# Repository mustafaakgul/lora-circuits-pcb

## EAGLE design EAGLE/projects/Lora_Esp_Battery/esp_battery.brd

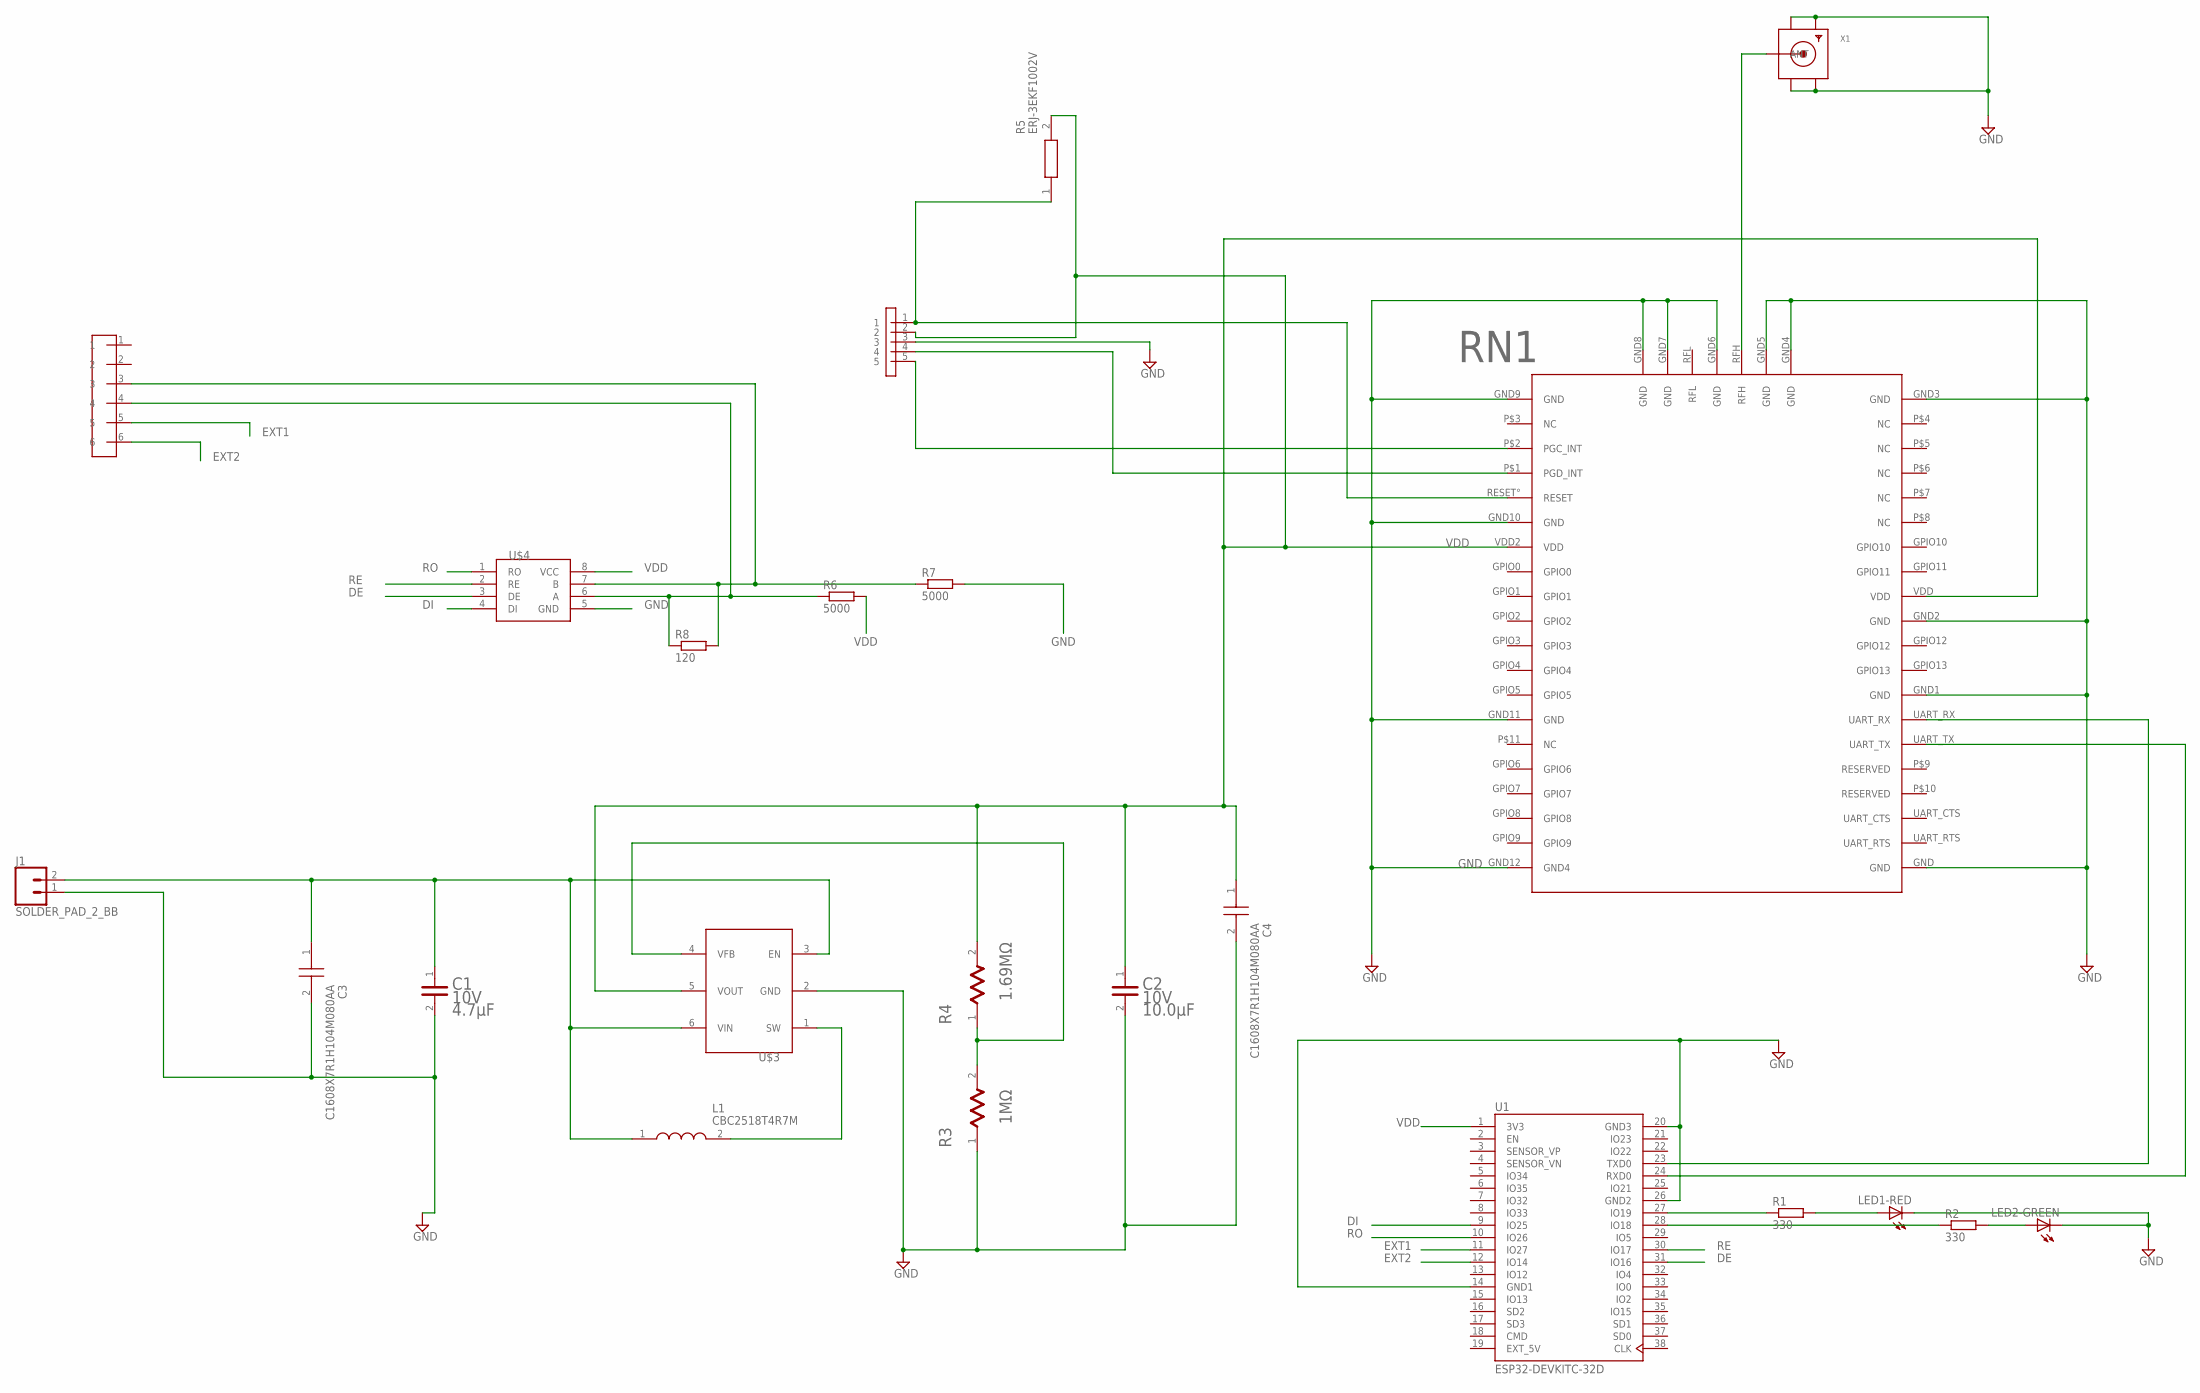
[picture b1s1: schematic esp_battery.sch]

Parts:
C1: KEMET_C0603C475K8PACTUKEMET_C0603C475K8PACTU_0_0; KEMET_C0603C475K8PACTU_0
C2: TDK_C1608X5R1A106M080ACTDK_C1608X5R1A106M080AC_0_0; TDK_C1608X5R1A106M080AC_0
C3, C4: C1608X7R1H104M080AA; CAPC1608X80N
J1: SOLDER_PAD_2_BB; SOLDER_PAD_2
L1: CBC2518T4R7M; INDC2518X200N
LED1-RED, LED2-GREEN: LEDCHIP-LED0603; CHIP-LED0603
R1, R2: 330; R0603
R3: STACKPOLE_RMCF0603FT1M00STACKPOLE_RMCF0603FT1M00_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; STACKPOLE_RMCF0603FT1M00_1
R4: VISHAY_CRCW06031M69FKEAVISHAY_CRCW06031M69FKEA_0_1; VISHAY_CRCW06031M69FKEA_1
R5: ERJ-3EKF1002V; RESC1608X55N
R6, R7: 5000; R0805
R8: 120; R0805
RN1: NEW_RN2483
U1: ESP32-DEVKITC-32D; MODULE_ESP32-DEVKITC-32D
U$1: CONNECTOR62; CONNECTOR6
U$2: ICSP52; ICSP
U$3: MCP16252
U$4: AMD3485E
X1: SMACONNECTOR_EDGE; SMA_EDGELAUNCH

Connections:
DE: U1.31 (IO16), U$4.3 (DE)
DI: U1.9 (IO25), U$4.4 (DI)
EXT1: U1.11 (IO27), U$1.5
EXT2: U1.12 (IO14), U$1.6
EXT_5V: U1.19 (EXT_5V)
GND: C1.2, C2.2, C3.2, C4.2, J1.1, LED1-RED.C, LED2-GREEN.C, R3.1, R7.2, RN1.GND, RN1.GND1 (GND), RN1.GND2 (GND), RN1.GND3 (GND), RN1.GND4 (GND), RN1.GND5 (GND), RN1.GND6 (GND), RN1.GND7 (GND), RN1.GND8 (GND), RN1.GND9 (GND), RN1.GND10 (GND), RN1.GND11 (GND), RN1.GND12 (GND4), U1.14 (GND1), U1.20 (GND3), U1.26 (GND2), U$2.3, U$3.2 (GND), U$4.5 (GND), X1.GND@1 (GND4), X1.GND@2 (GND3), X1.GND@3 (GND2), X1.GND@4 (GND1)
unnamed: R1.1, U1.27 (IO19)
unnamed: LED1-RED.A, R1.2
unnamed: C1.1, C3.1, J1.2, L1.1, U$3.3 (EN), U$3.6 (VIN)
unnamed: LED2-GREEN.A, R2.2
unnamed: R2.1, U1.28 (IO18)
unnamed: R5.1, RN1.RESET° (RESET), U$2.1
unnamed: RN1.RFH, X1.P (ANT)
unnamed: L1.2, U$3.1 (SW)
unnamed: R3.2, R4.1, U$3.4 (VFB)
unnamed: RN1.P$1 (PGD_INT), U$2.4
unnamed: RN1.P$2 (PGC_INT), U$2.5
unnamed: RN1.UART_RX, U1.23 (TXD0)
unnamed: R7.1, R8.2, U$1.3, U$4.7 (B)
unnamed: R6.1, R8.1, U$1.4, U$4.6 (A)
unnamed: RN1.UART_TX, U1.24 (RXD0)
RE: U1.30 (IO17), U$4.2 (RE)
RO: U1.10 (IO26), U$4.1 (RO)
VDD: C2.1, C4.1, R4.2, R5.2, R6.2, RN1.VDD, RN1.VDD2 (VDD), U1.1 (3V3), U$2.2, U$3.5 (VOUT), U$4.8 (VCC)

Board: 2 copper layers, 23 parts (1 on the bottom side), 23 nets, no tracks yet.

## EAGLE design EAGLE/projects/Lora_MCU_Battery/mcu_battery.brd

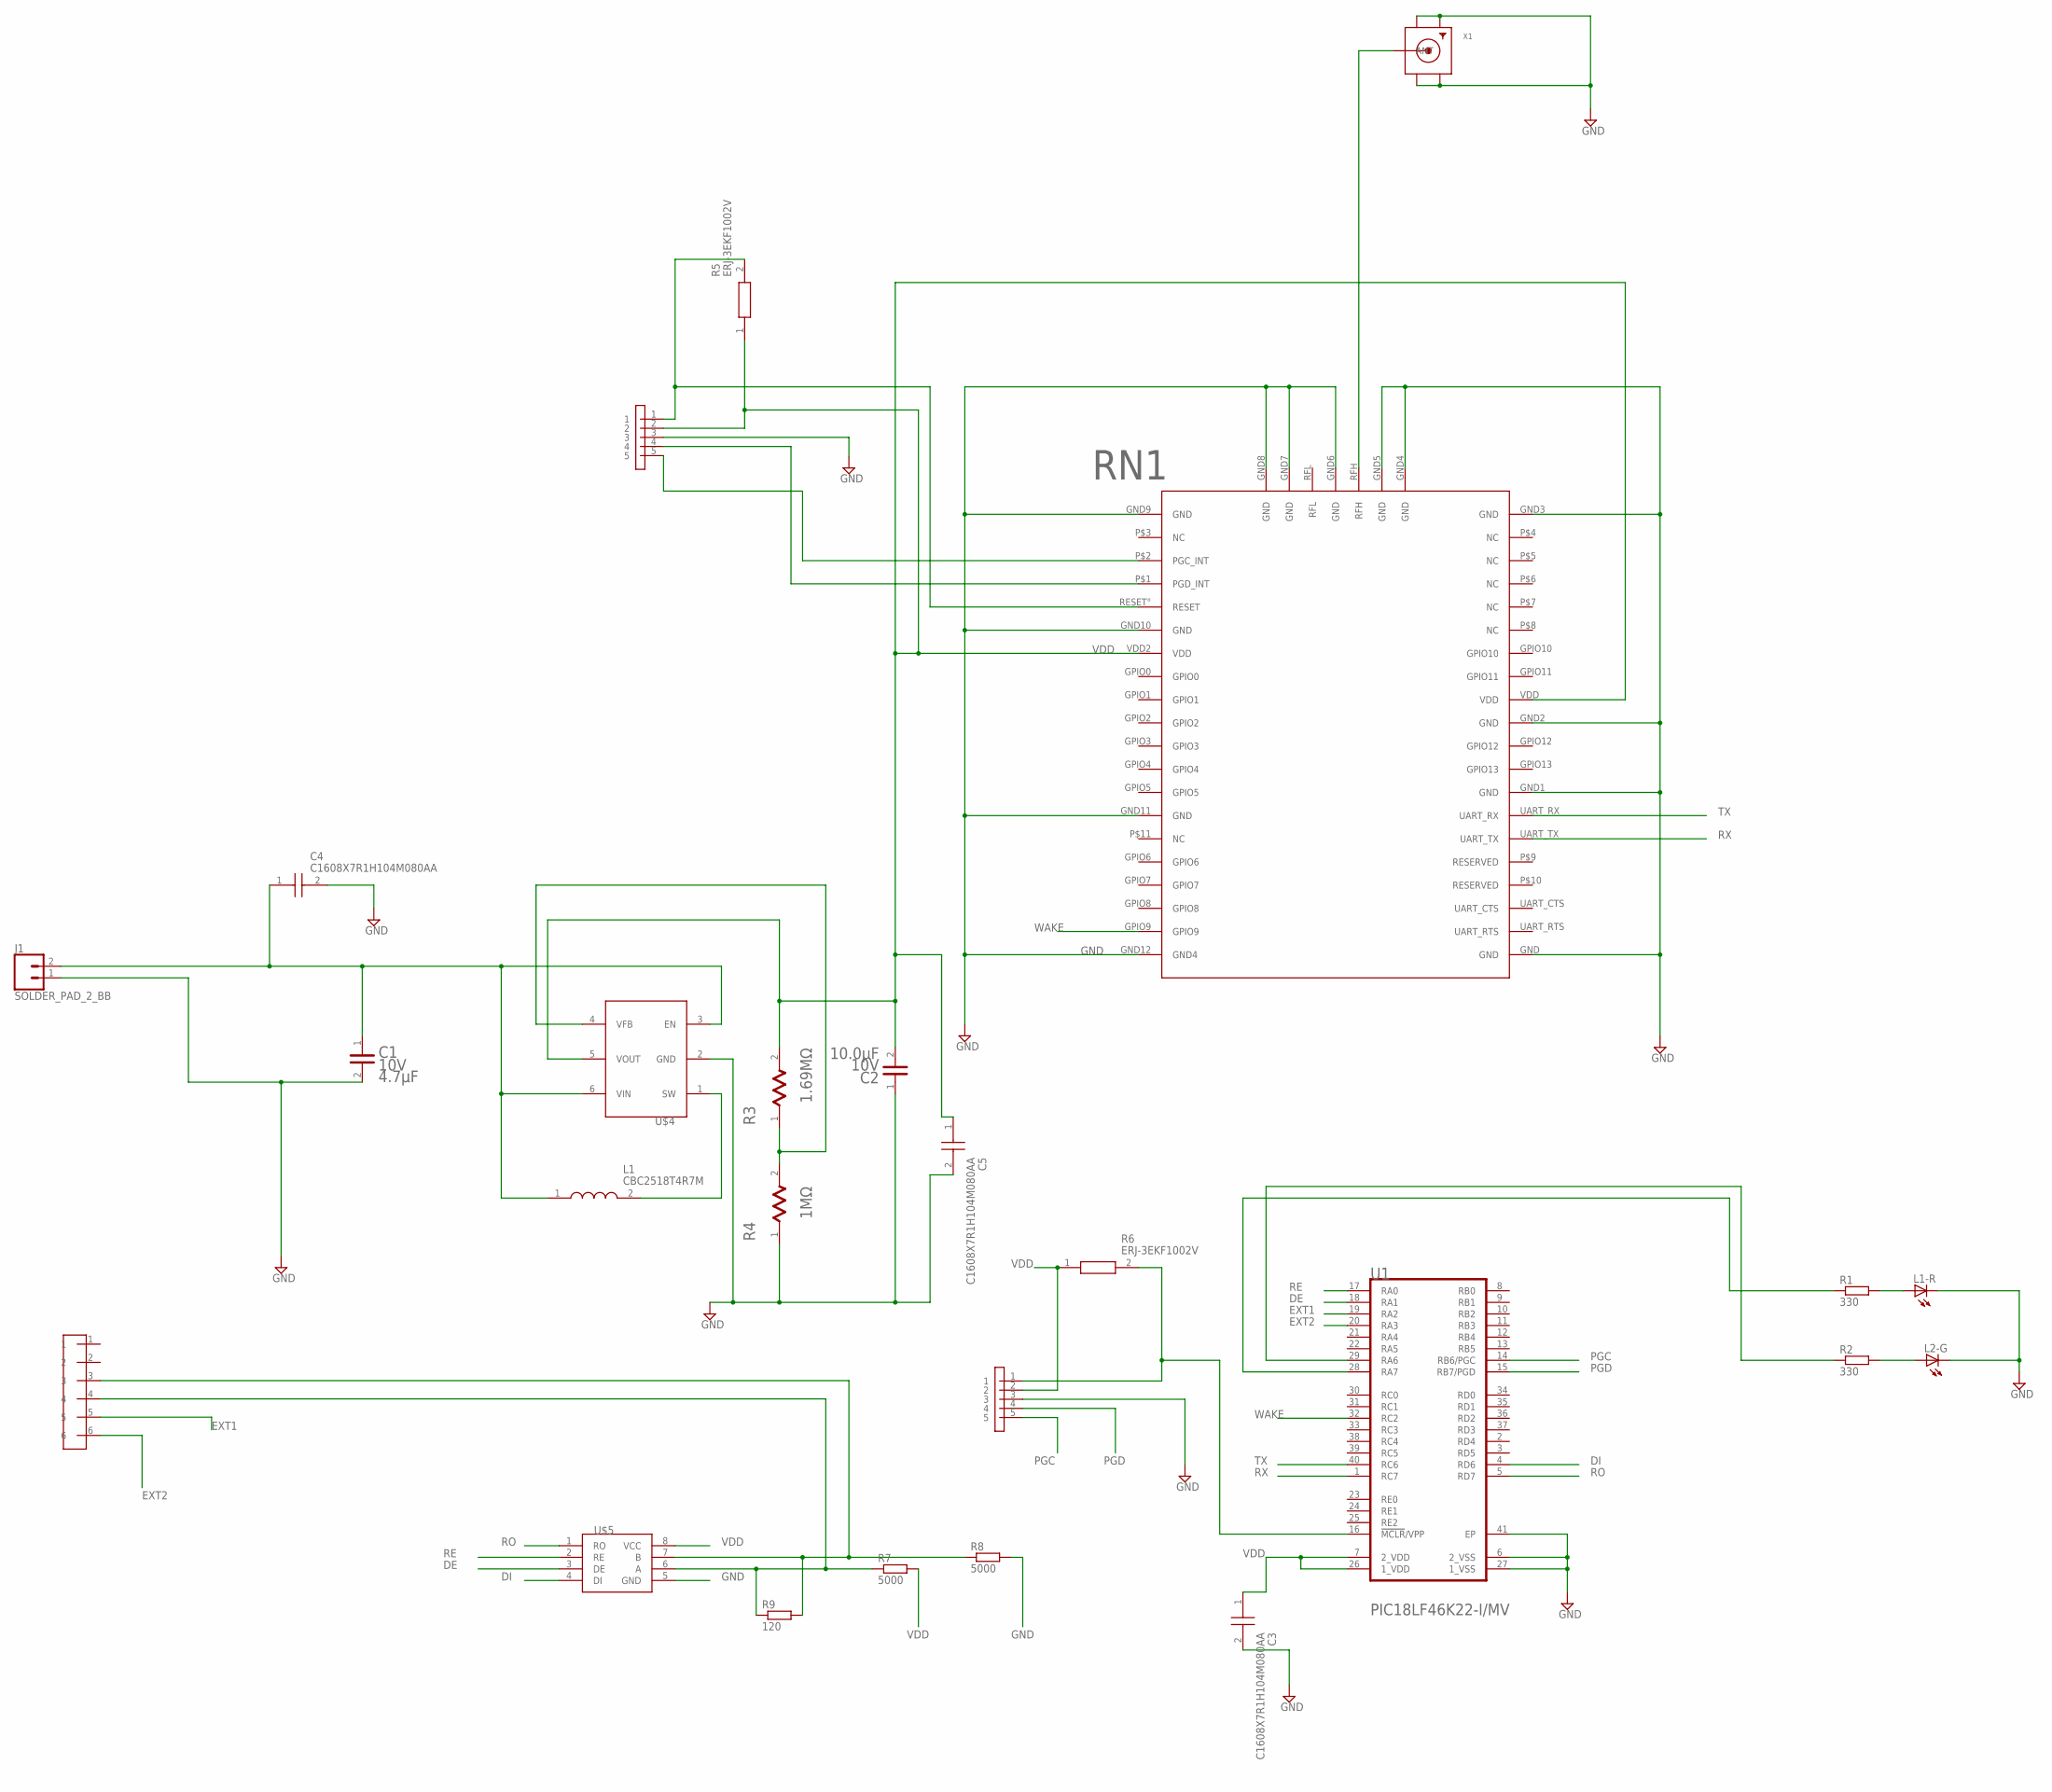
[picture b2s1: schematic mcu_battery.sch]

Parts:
C1: KEMET_C0603C475K8PACTUKEMET_C0603C475K8PACTU_0_0; KEMET_C0603C475K8PACTU_0
C2: TDK_C1608X5R1A106M080ACTDK_C1608X5R1A106M080AC_0_0; TDK_C1608X5R1A106M080AC_0
C3, C4, C5: C1608X7R1H104M080AA; CAPC1608X80N
J1: SOLDER_PAD_2_BB; SOLDER_PAD_2
L1: CBC2518T4R7M; INDC2518X200N
L1-R, L2-G: LEDCHIP-LED0603; CHIP-LED0603
R1, R2: 330; R0603
R3: VISHAY_CRCW06031M69FKEAVISHAY_CRCW06031M69FKEA_0_1; VISHAY_CRCW06031M69FKEA_1
R4: STACKPOLE_RMCF0603FT1M00STACKPOLE_RMCF0603FT1M00_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; STACKPOLE_RMCF0603FT1M00_1
R5, R6: ERJ-3EKF1002V; RESC1608X55N
R7, R8: 5000; R0805
R9: 120; R0805
RN1: NEW_RN2483
U1: MICROCHIP_PIC18LF46K22-I-MVMICROCHIP_PIC18LF46K22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; MICROCHIP_PIC18LF46K22-I-MV_1
U$1: CONNECTOR62; CONNECTOR6
U$2, U$3: ICSP52; ICSP
U$4: MCP16252
U$5: AMD3485E
X1: SMACONNECTOR_EDGE; SMA_EDGELAUNCH

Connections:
DE: U1.18 (RA1), U$5.3 (DE)
DI: U1.4 (RD6), U$5.4 (DI)
EXT1: U1.19 (RA2), U$1.5
EXT2: U1.20 (RA3), U$1.6
GND: C1.2, C2.1, C3.2, C4.2, C5.2, J1.1, L1-R.C, L2-G.C, R4.1, R8.2, RN1.GND, RN1.GND1 (GND), RN1.GND2 (GND), RN1.GND3 (GND), RN1.GND4 (GND), RN1.GND5 (GND), RN1.GND6 (GND), RN1.GND7 (GND), RN1.GND8 (GND), RN1.GND9 (GND), RN1.GND10 (GND), RN1.GND11 (GND), RN1.GND12 (GND4), U1.6 (2_VSS), U1.27 (1_VSS), U1.41 (EP), U$2.3, U$3.3, U$4.2 (GND), U$5.5 (GND), X1.GND@1 (GND4), X1.GND@2 (GND3), X1.GND@3 (GND2), X1.GND@4 (GND1)
MCLR: R6.2, U1.16 (!MCLR!/VPP), U$2.1
unnamed: R2.1, U1.29 (RA6)
unnamed: L2-G.A, R2.2
unnamed: R1.1, U1.28 (RA7)
unnamed: C1.1, C4.1, J1.2, L1.1, U$4.3 (EN), U$4.6 (VIN)
unnamed: L1-R.A, R1.2
unnamed: L1.2, U$4.1 (SW)
unnamed: R5.2, RN1.RESET° (RESET), U$3.1
unnamed: RN1.RFH, X1.P (ANT)
unnamed: R3.1, R4.2, U$4.4 (VFB)
unnamed: RN1.P$2 (PGC_INT), U$3.5
unnamed: RN1.P$1 (PGD_INT), U$3.4
unnamed: R8.1, R9.2, U$1.3, U$5.7 (B)
unnamed: R7.1, R9.1, U$1.4, U$5.6 (A)
PGC: U1.14 (RB6/PGC), U$2.5
PGD: U1.15 (RB7/PGD), U$2.4
RE: U1.17 (RA0), U$5.2 (RE)
RO: U1.5 (RD7), U$5.1 (RO)
RX: RN1.UART_TX, U1.1 (RC7)
TX: RN1.UART_RX, U1.40 (RC6)
VDD: C2.2, C3.1, C5.1, R3.2, R5.1, R6.1, R7.2, RN1.VDD, RN1.VDD2 (VDD), U1.7 (2_VDD), U1.26 (1_VDD), U$2.2, U$3.2, U$4.5 (VOUT), U$5.8 (VCC)
WAKE: RN1.GPIO9, U1.32 (RC2)

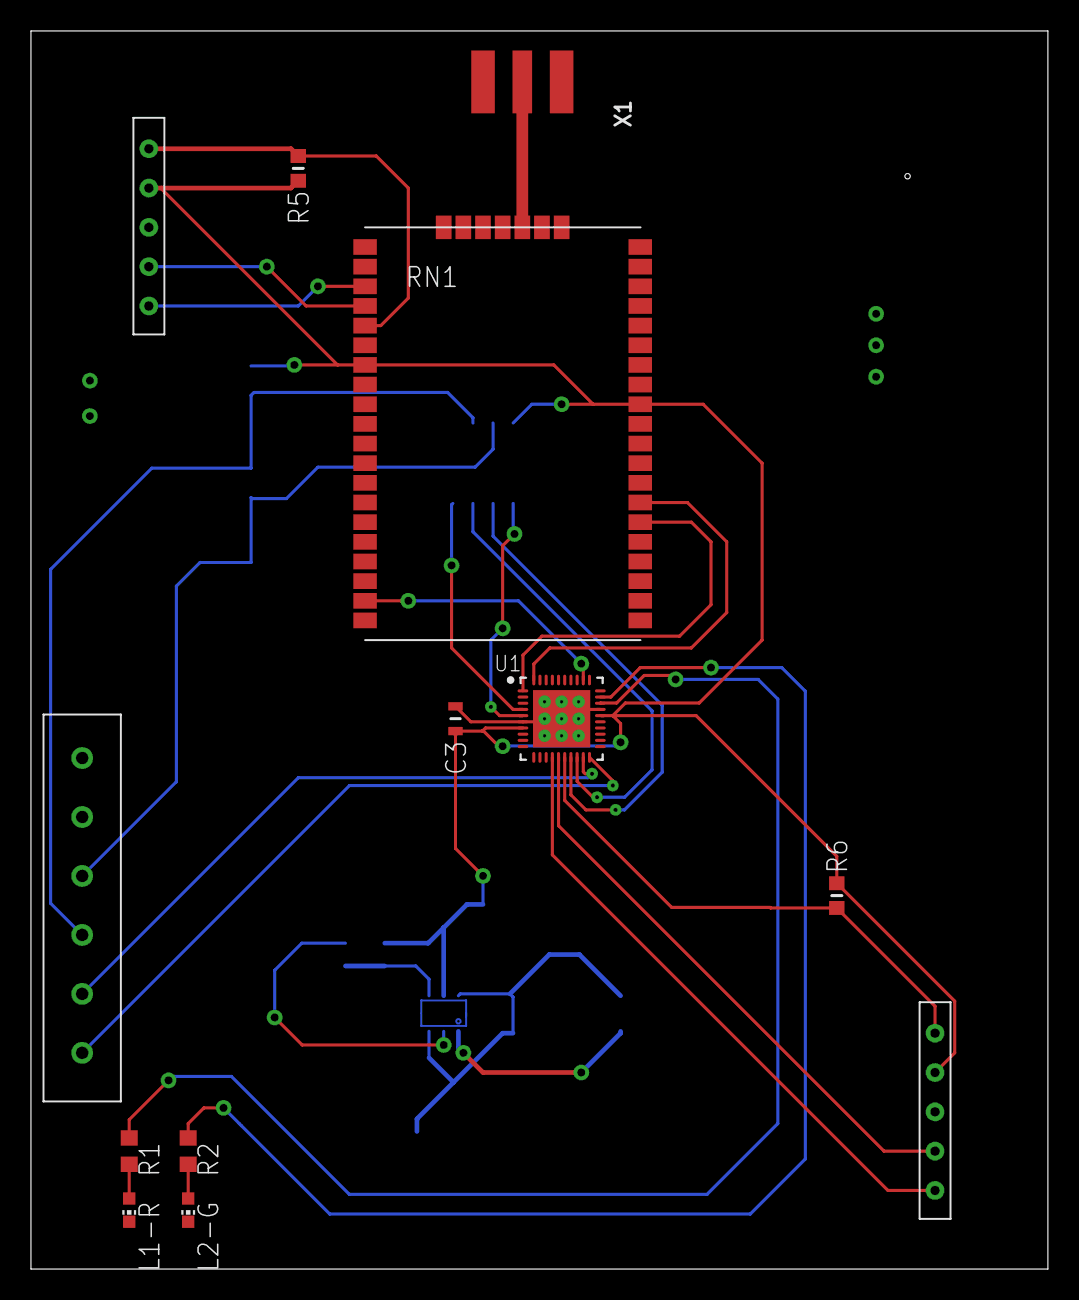
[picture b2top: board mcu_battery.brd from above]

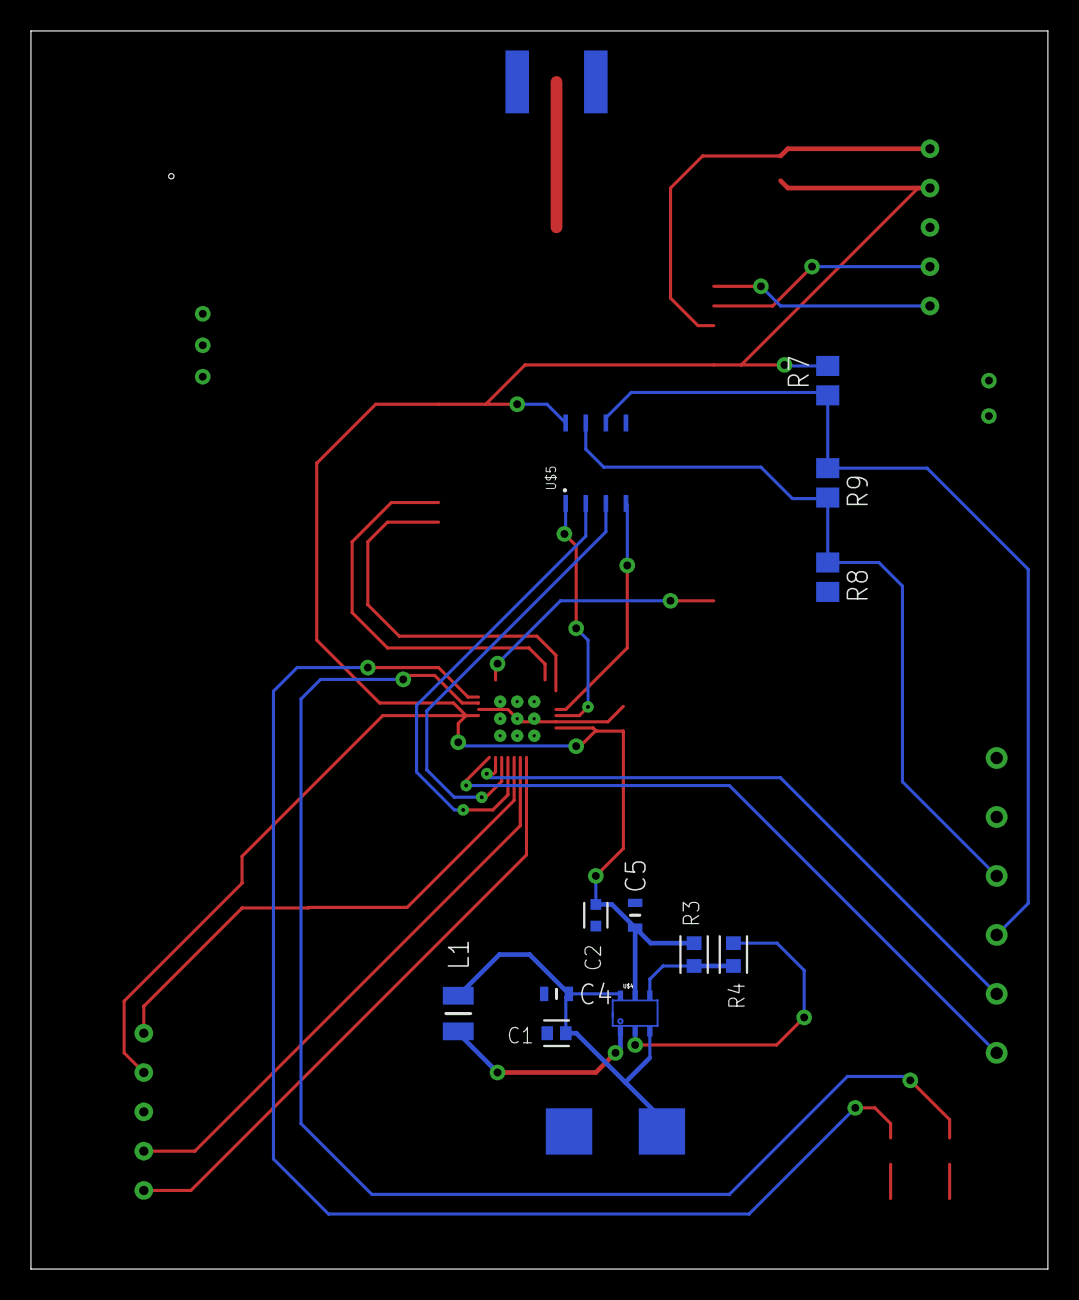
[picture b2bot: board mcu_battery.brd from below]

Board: 2 copper layers, 65.7 x 80.0 mm, 26 parts (13 on the bottom side), 27 nets.

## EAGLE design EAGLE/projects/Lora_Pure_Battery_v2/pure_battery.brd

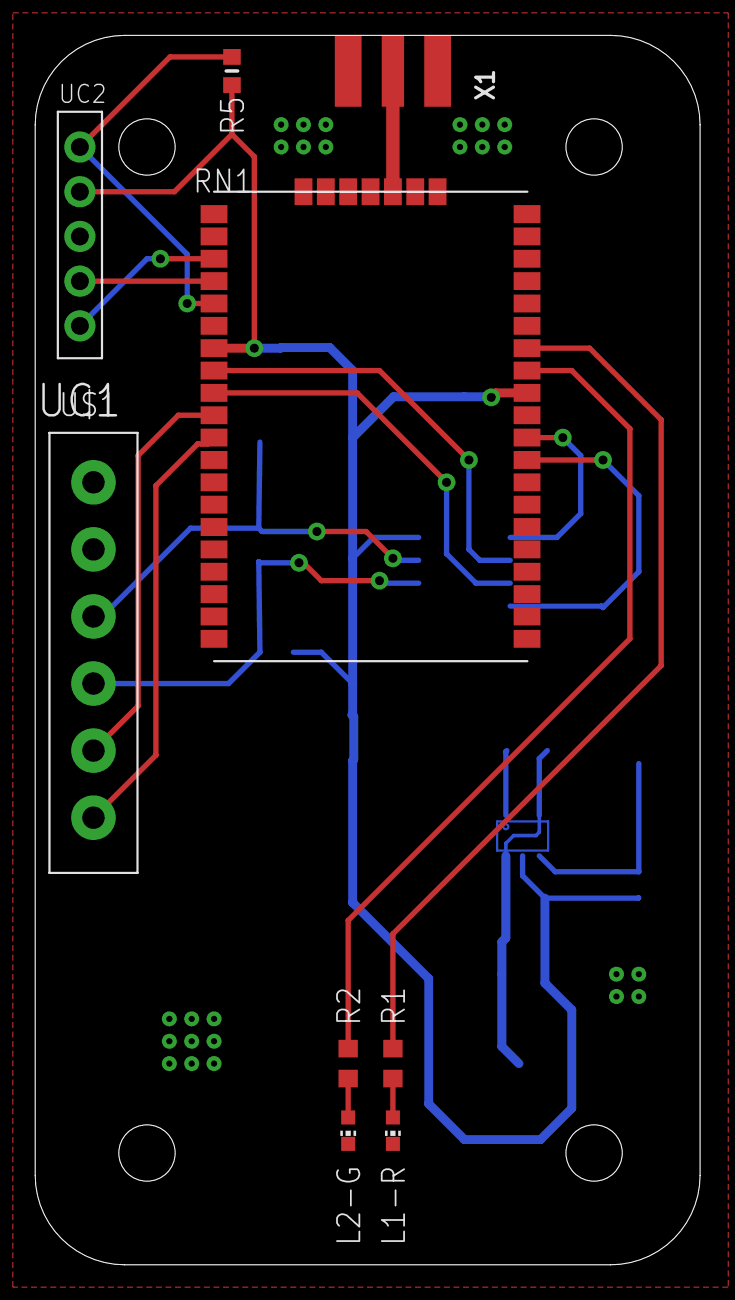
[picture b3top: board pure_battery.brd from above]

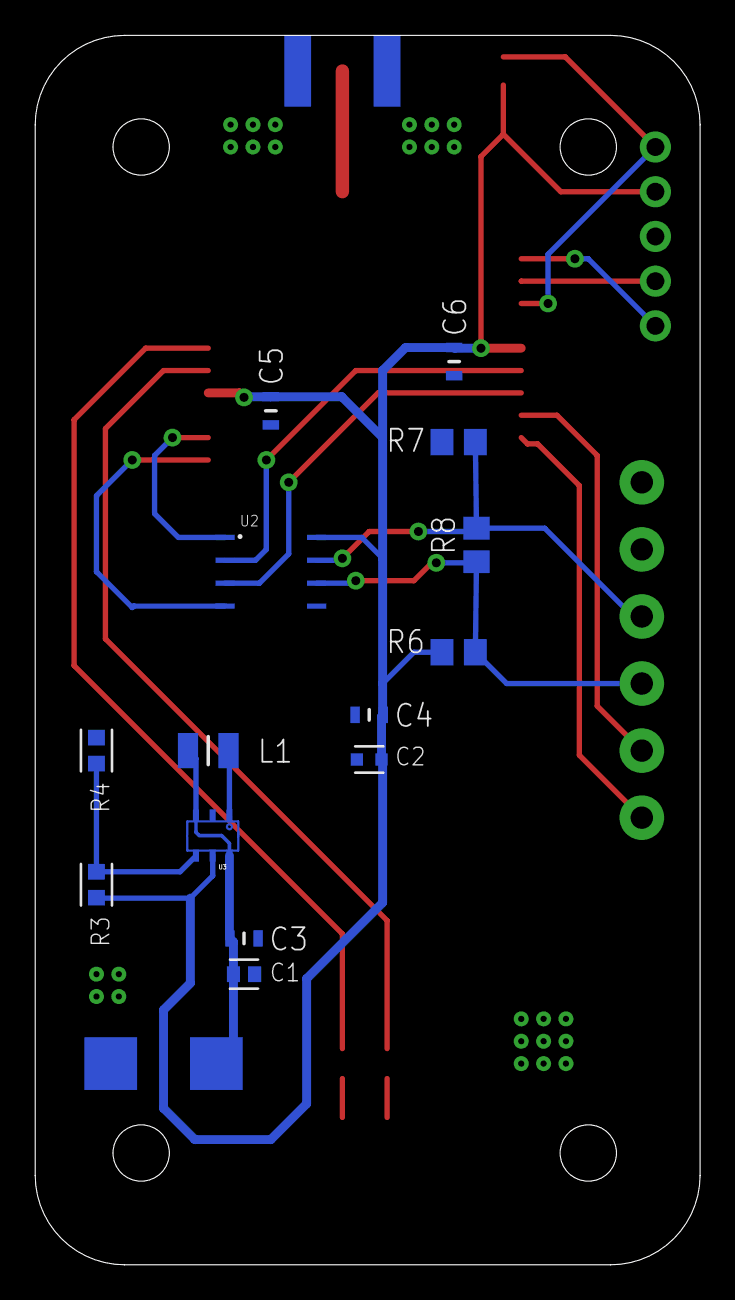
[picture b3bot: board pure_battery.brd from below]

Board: 2 copper layers, 37.8 x 69.8 mm, 24 parts (15 on the bottom side), 21 nets.

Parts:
C1: KEMET_C0603C475K8PACTUKEMET_C0603C475K8PACTU_0_0; KEMET_C0603C475K8PACTU_0
C2: TDK_C1608X5R1A106M080ACTDK_C1608X5R1A106M080AC_0_0; TDK_C1608X5R1A106M080AC_0
C3, C4, C5, C6: C1608X7R1H104M080AA; CAPC1608X80N
J1: SOLDER_PAD_2_BB; SOLDER_PAD_2
L1: CBC2518T4R7M; INDC2518X200N
L1-R, L2-G: CHIP-LED0603
R1, R2: 330; R0603
R3: VISHAY_CRCW06031M69FKEAVISHAY_CRCW06031M69FKEA_0_1; VISHAY_CRCW06031M69FKEA_1
R4: STACKPOLE_RMCF0603FT1M00STACKPOLE_RMCF0603FT1M00_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; STACKPOLE_RMCF0603FT1M00_1
R5: ERJ-3EKF1002V; RESC1608X55N
R6, R7: 5000; R0805
R8: 120; R0805
RN1: NEW_RN2483
U2: AMD3485E
U3: MCP16252
U$1: CONNECTOR6_V2
U$2: ICSP_V2
X1: SMA_EDGELAUNCH

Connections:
A: R6.2, R8.1, U2.6, U$1.4
B: R7.2, R8.2, U2.7, U$1.3
DE: RN1.GPIO1, U2.3
DI: RN1.GPIO13, U2.4
GND: C1.2, C2.1, C3.2, C4.2, C5.2, C6.2, J1.1, L1-R.C, L2-G.C, R4.1, R7.1, RN1.GND, RN1.GND1, RN1.GND2, RN1.GND3, RN1.GND4, RN1.GND5, RN1.GND6, RN1.GND7, RN1.GND8, RN1.GND9, RN1.GND10, RN1.GND11, RN1.GND12, U2.5, U3.2, U$2.3, X1.GND@1, X1.GND@2, X1.GND@3, X1.GND@4
GPIO2: RN1.GPIO2, U$1.5
GPIO3: RN1.GPIO3, U$1.6
unnamed: R1.1, RN1.GPIO10
unnamed: L1-R.A, R1.2
unnamed: C1.1, C3.1, J1.2, L1.1, U3.3, U3.6
unnamed: R2.1, RN1.GPIO11
unnamed: L2-G.A, R2.2
unnamed: RN1.P$2, U$2.5
unnamed: L1.2, U3.1
unnamed: R3.1, R4.2, U3.4
unnamed: RN1.P$1, U$2.4
unnamed: R5.2, RN1.RESET°, U$2.1
unnamed: RN1.RFH, X1.P
RE: RN1.GPIO0, U2.2
RO: RN1.GPIO12, U2.1
VCC: C2.2, C4.1, C5.1, C6.1, R3.2, R5.1, R6.1, RN1.VDD, RN1.VDD2, U2.8, U3.5, U$2.2

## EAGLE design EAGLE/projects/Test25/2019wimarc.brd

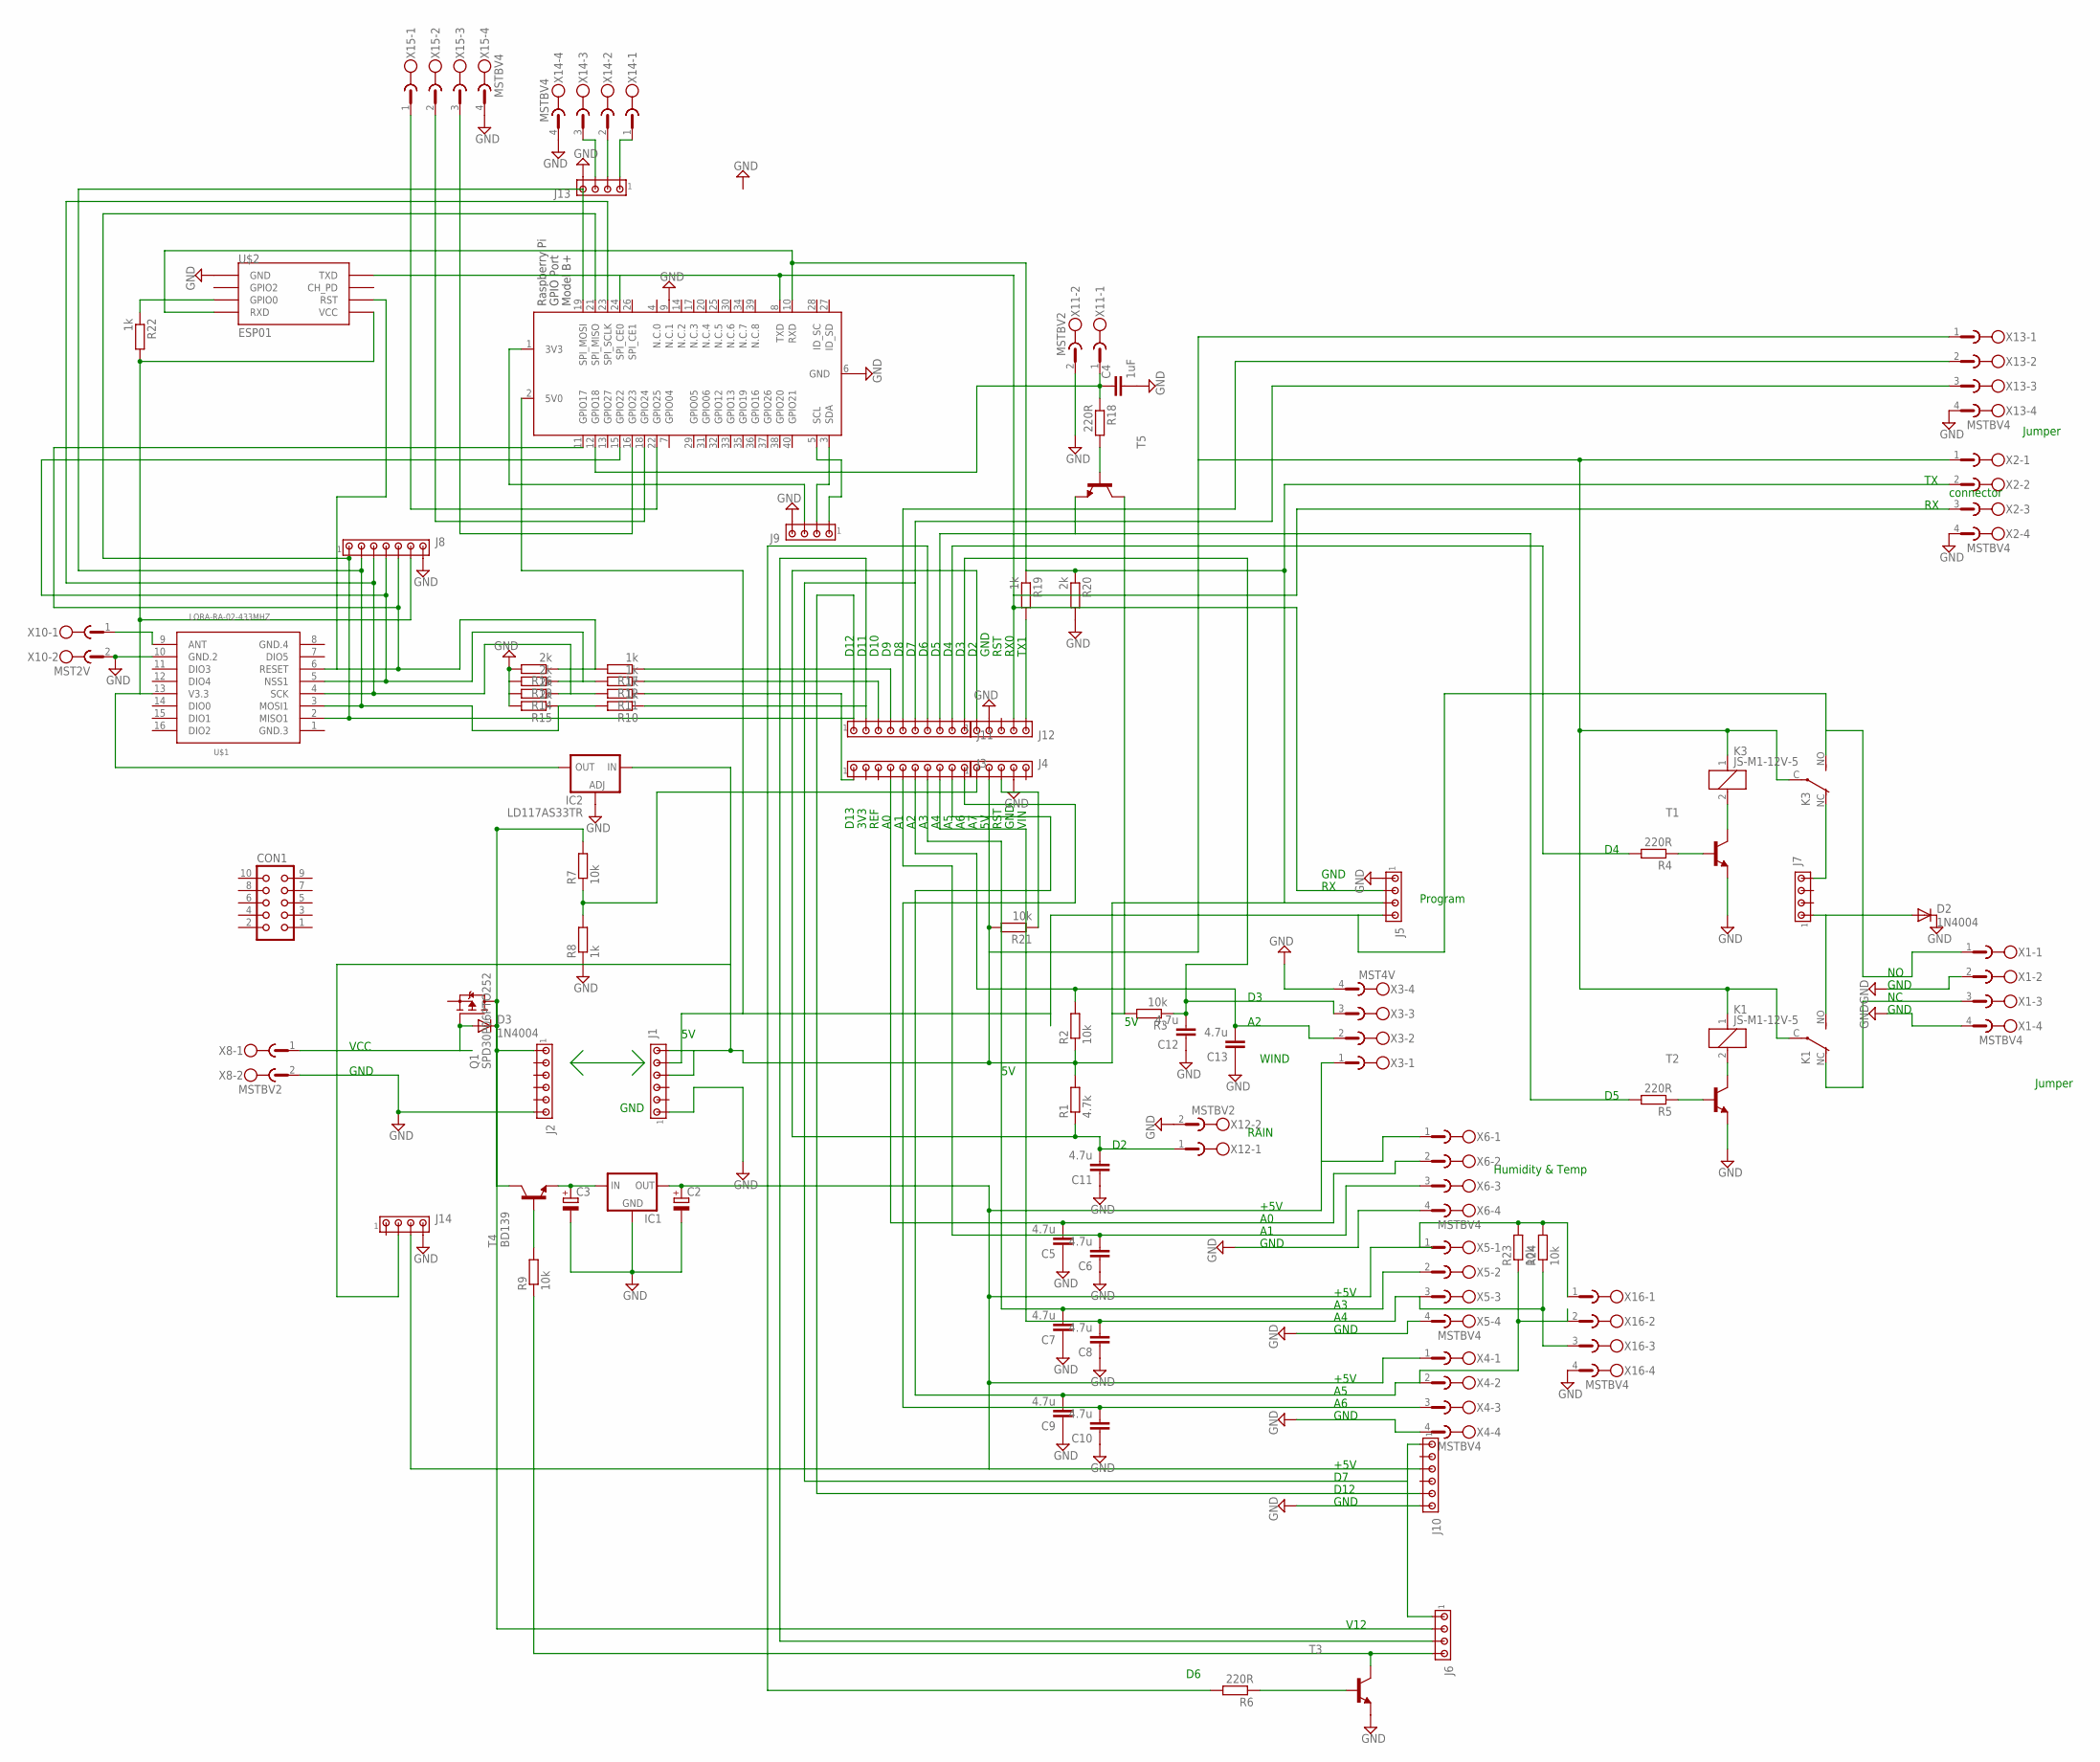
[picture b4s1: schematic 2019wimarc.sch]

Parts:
C2, C3: CPOL-EUE2.5-7; E2,5-7
C4: 1uF; C0805K
C5, C6, C7, C8, C9, C10, C11, C12, C13: 4.7u; C0805K
CON1: CON10
D2, D3: 1N4004; DO41-10
IC1: 78XXL
IC2: LD117AS33TR; SOT223
J1, J2, J10: MTA06-100; 10X06MTA
J3, J11: MTA10-100; 10X10MTA
J4, J12: MTA05-100; 10X05MTA
J5, J6, J7, J9, J13, J14: MTA04-100; 10X04MTA
J8: MTA07-100; 10X07MTA
K1, K3: JS-M1-12V-5; JS-M
Q1: SPD30P06PTO252; TO252
R1: 4.7k; M0805
R2, R3, R7, R9, R21, R23, R24: 10k; M0805
R4, R5, R6, R18: 220R; M0805
R8, R10, R11, R12, R17, R19, R22: 1k; M0805
R13, R14, R15, R16, R20: 2k; M0805
T1, T2, T3, T5: -NPN-SOT89-BCE; SOT89-BCE
T4: BD139; TO126
U$1: LORA-RA-02-433MHZ; LORA-RA2-SMD
U$2: ESP01
X1, X2, X4, X5, X6, X13, X14, X15, X16: MSTBV4
X3: MST4V; MSTBV4
X8, X11, X12: MSTBV2
X9: RASPI_BOARD_B+_F; RASPI_BOARD_B+_FULL
X10: MST2V; MSTBV2

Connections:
DIO3: U$1.11 (DIO3)
GND: C2.-, C3.-, C4.2, C5.1, C6.1, C7.1, C8.1, C9.1, C10.1, C11.1, C12.1, C13.1, D2.C, IC1.GND, IC2.1 (ADJ), J1.1, J2.6, J4.4, J5.1, J8.7, J9.4, J10.6, J12.2, J13.4, J14.4, R8.1, R13.2, R14.2, R15.2, R16.2, R20.2, T1.E, T2.E, T3.E, U$1.10 (GND.2), U$2.GND, X1.2, X1.4, X2.4, X3.4, X4.4, X5.4, X6.4, X8.2, X9.6 (GND), X9.9 (N.C.1), X10.2, X11.2, X12.2, X13.4, X14.4, X15.4, X16.4
GND.3: U$1.1 (GND.3)
GND.4: U$1.8 (GND.4)
unnamed: C5.2, J3.4, X6.2
unnamed: C11.2, J12.1, R1.1, X12.1
unnamed: C12.2, J11.10, R3.1, X3.3
unnamed: C13.2, J3.6, R2.2, X3.2
unnamed: J7.4, K3.NC (O)
unnamed: J3.1, R11.1
unnamed: D3.A, Q1.1 (G), X8.1
unnamed: R19.1, R20.1, U$2.RX (RXD), X2.2, X9.10 (RXD)
unnamed: J5.2, J12.4, U$2.TX (TXD), X2.3, X9.8 (TXD)
unnamed: J13.1, X14.1
unnamed: J11.3, R12.1
unnamed: D3.C, J2.1, J6.2, Q1.3 (D), R7.2, T4.2 (C)
unnamed: C6.2, J3.5, X6.3
unnamed: C7.2, J3.7, X5.2
unnamed: C8.2, J3.8, R24.1, X5.3, X16.3
unnamed: C10.2, J3.10, X4.3
unnamed: J11.6, X13.3
unnamed: J8.1, J10.5, J11.1, U$1.2 (MISO1), X9.21 (SPI_MISO)
unnamed: K3.2, T1.C
unnamed: X9.22 (GPIO25), X15.1
unnamed: R4.1, T1.B
unnamed: K1.2, T2.C
unnamed: R5.1, T2.B
unnamed: K1.NC (O), X1.3
unnamed: J6.4, R9.1, T3.C
unnamed: C2.+, IC1.OUT, J10.3, J14.3, R23.2, R24.2, X3.1, X4.1, X5.1, X6.1, X16.1
unnamed: J4.1, R7.1, R8.2
unnamed: R6.1, T3.B
unnamed: J11.9, R4.2
unnamed: J11.8, R5.2, T5.E
unnamed: J11.7, R6.2
unnamed: J6.1, J10.1
unnamed: J8.3, R11.2, R14.1, U$1.4 (SCK), X9.23 (SPI_SCLK)
unnamed: D2.A, J7.1, K1.NO (S)
unnamed: R18.2, T5.B
unnamed: C3.+, IC1.IN, T4.1 (E)
unnamed: R9.2, T4.3 (B)
unnamed: J11.5, X13.2
unnamed: X9.18 (GPIO24), X15.2
unnamed: J8.5, R16.1, R17.2, U$1.6 (RESET), U$2.RST, X9.11 (GPIO17)
unnamed: J8.2, R10.2, R15.1, U$1.3 (MOSI1), X9.19 (SPI_MOSI)
unnamed: J11.4, R17.1
unnamed: C4.1, R18.1, X9.12 (GPIO18), X11.1
unnamed: U$1.9 (ANT), X10.1
unnamed: J8.4, R12.2, R13.1, U$1.5 (NSS1), X9.15 (GPIO22)
unnamed: J12.5, R19.2
unnamed: J4.3, R21.1
unnamed: J9.2, X9.3 (SDA)
unnamed: J9.1, X9.5 (SCL)
unnamed: IC2.4 (OUT), J8.6, R22.2, U$1.13 (V3.3), U$2.VCC
unnamed: IC2.3 (IN), J1.4, J1.6, J4.2, J5.3, J14.2, K1.1, K1.C, K3.1, K3.C, R1.2, R2.1, R3.2, R21.2, T5.C, X2.1, X13.1
unnamed: J13.2, X14.2
unnamed: J13.3, X14.3
unnamed: X9.16 (GPIO23), X15.3
unnamed: J6.3, J11.2, R10.1
unnamed: J9.3, X9.1 (3V3)
unnamed: R22.1, U$2.GPIO0
unnamed: C9.2, J3.9, R23.1, X4.2, X16.2
unnamed: J1.5, J5.4, K3.NO (S), X1.1, X9.2 (5V0)

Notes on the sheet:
D13
3V3
REF
RST
GND
VIN
TX1
RX0
D10
D11
D12
Program
WIND
RAIN
+5V
Humidity & Temp
Jumper
connector
VCC
V12

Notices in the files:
parts and their libraries:
SparkFun-Connectors: Licensing: Creative Commons ShareAlike 4.0 International - https://creativecommons.org/licenses/by-sa/4.0
